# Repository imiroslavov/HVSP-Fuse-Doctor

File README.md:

# HVSP Fuse Doctor

The story began a long time ago. As of the moment that I am writing this README.md almost 21 years passed since then. 
I was really passionate to learn how to design and make my own hardware so I started learning how to make my own schematics, PCBs and how to program microcontrollers. 
Unfortunately I didn't knew how to properly program fuses and what was the difference between a crystal and clock oscillator so I ended up with a pile of "dead" microcontrollers. 
Back in these days I had a self made High-voltage programmer (The almighty "ByteBlaster+". I will post schematics and board design on another repository) but nowadays I have no place to plug it in since LPT ports are long time out of use in modern computing. 
I was developing a Low-ohm continuity tester with ATtiny2313 and accidentally bricked the MCU in my personal "old-school style" way (I've pulled my beard at least 1cm longer) and guess what... 
It was the last one in the box that was alive. So the journey began. 
I've ended up finding a lot of schematics and information, but most of it was related to using Arduino which for me was just a big "Ehh!". 
I found a few blog posts which helped me to design the device to be dependent on the power supply only (credits on the end of the page).

## Pinout

| PIN  | AVR | HVSP |
| ------------- | ------------- | ------------- |
| 1 | PC5 | **12V / RST** |
| 2 | PC0 | **SDI** |
| 3 | PC1 | **SII** |
| 4 | PC2 | **SDO** |
| 5 | PC3 | **SCI** |
| 6 | PC4 | **5V / VCC** |
| 7 | GND | **GND** |

## Schematics
This is the base schematic. Version 2 contains additional header connected to PD1 and GND which is used for RS232 communication and can be omitted. Thus the connector it's not shown here because it is optional.

## Board prototype v1 (dual power supply 5V/12V)
|                                                    Bottom layer                                                    |                                                              Top view                                                               |
|:------------------------------------------------------------------------------------------------------------------:|:-----------------------------------------------------------------------------------------------------------------------------------:|
|  |  |

Please note that the main.sch has additional sheet containing the mounting pads and connectors not shown in the schematics diagram above. They are there, but feel free to change them to make your own design (I've used one of those power supplies for external SATA disk drive readers that provide 5 and 12 volts simultaneously (DIN6)). 

## Notes
If the system still does not answer for a simple ISP programmer, that means the MCU has damaged hardware SPI, other damage or bad EEPROM.

Thanks to Peter Fleury at http://www.peterfleury.epizy.com/ for the original schematics and code. I've changed it of course but it is based on his work.

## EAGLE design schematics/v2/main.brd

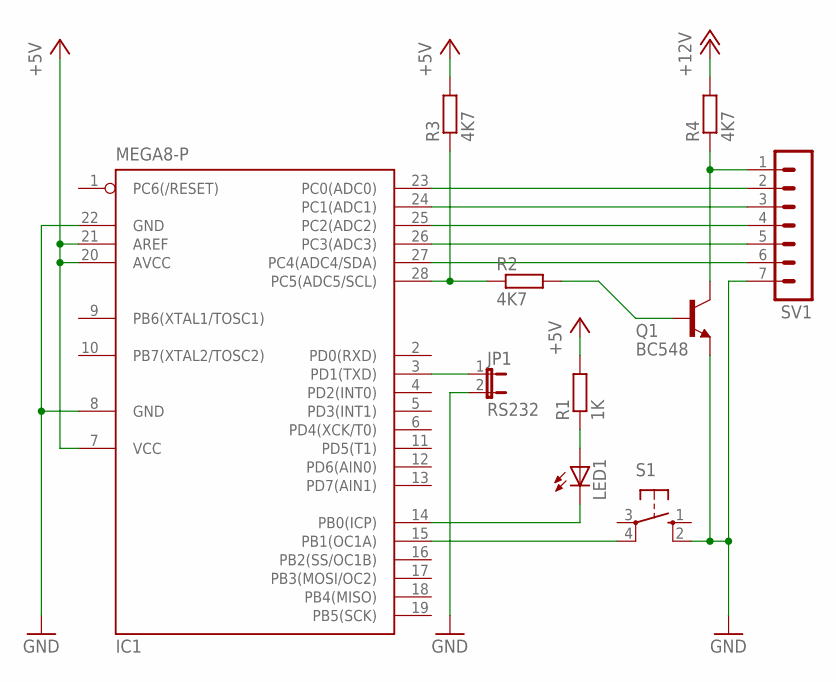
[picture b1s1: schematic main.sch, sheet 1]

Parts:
IC1: MEGA8-P; DIL28-3
JP1: RS232; JP1
LED1: LED5MM
Q1: BC548; TO92-EBC
R1: 1K; 0204/7
R2, R3, R4: 4K7; 0204/7
S1: 40-XX; B3F-40XX
SV1: MA07-1

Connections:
+5V: IC1.7 (VCC), IC1.20 (AVCC), IC1.21 (AREF), R1.2, R3.2; also elsewhere on the board
+12V: R4.2; also elsewhere on the board
GND: IC1.8 (GND), IC1.22 (GND), JP1.2, Q1.E, S1.2 (S1), SV1.7; also elsewhere on the board
unnamed: IC1.15 (PB1(OC1A)), S1.4 (P1)
unnamed: IC1.14 (PB0(ICP)), LED1.K (C)
unnamed: LED1.A, R1.1
unnamed: IC1.27 (PC4(ADC4/SDA)), SV1.6
unnamed: Q1.B, R2.2
unnamed: Q1.C, R4.1, SV1.1
unnamed: IC1.28 (PC5(ADC5/SCL)), R2.1, R3.1
unnamed: IC1.26 (PC3(ADC3)), SV1.5
unnamed: IC1.25 (PC2(ADC2)), SV1.4
unnamed: IC1.24 (PC1(ADC1)), SV1.3
unnamed: IC1.23 (PC0(ADC0)), SV1.2
unnamed: IC1.3 (PD1(TXD)), JP1.1

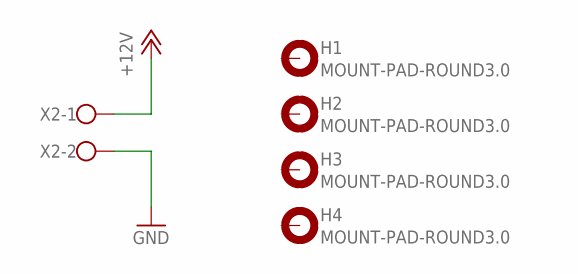
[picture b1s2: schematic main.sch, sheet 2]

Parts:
H1, H2, H3, H4: MOUNT-PAD-ROUND3.0; 3,0-PAD
X2: W237-102

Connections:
+12V: X2.1; also elsewhere on the board
GND: X2.2; also elsewhere on the board

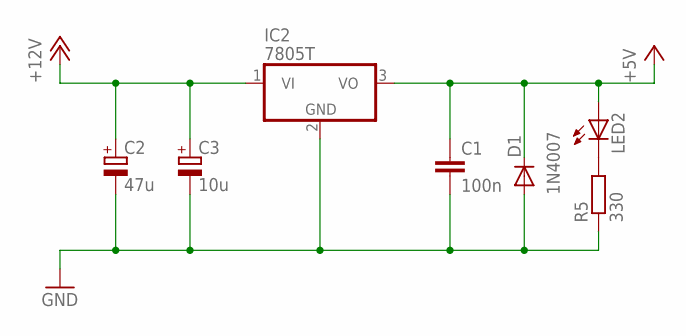
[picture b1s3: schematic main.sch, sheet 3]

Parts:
C1: 100n; C025-025X050
C2: 47u; E2,5-6
C3: 10u; E2,5-6
D1: 1N4007; D-7.5
IC2: 7805T; TO220H
LED2: LED5MM
R5: 330; 0204/7

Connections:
+5V: C1.1, D1.C, IC2.3 (VO), LED2.A; also elsewhere on the board
+12V: C2.+, C3.+, IC2.1 (VI); also elsewhere on the board
GND: C1.2, C2.-, C3.-, D1.A, IC2.2 (GND), R5.1; also elsewhere on the board
unnamed: LED2.K (C), R5.2

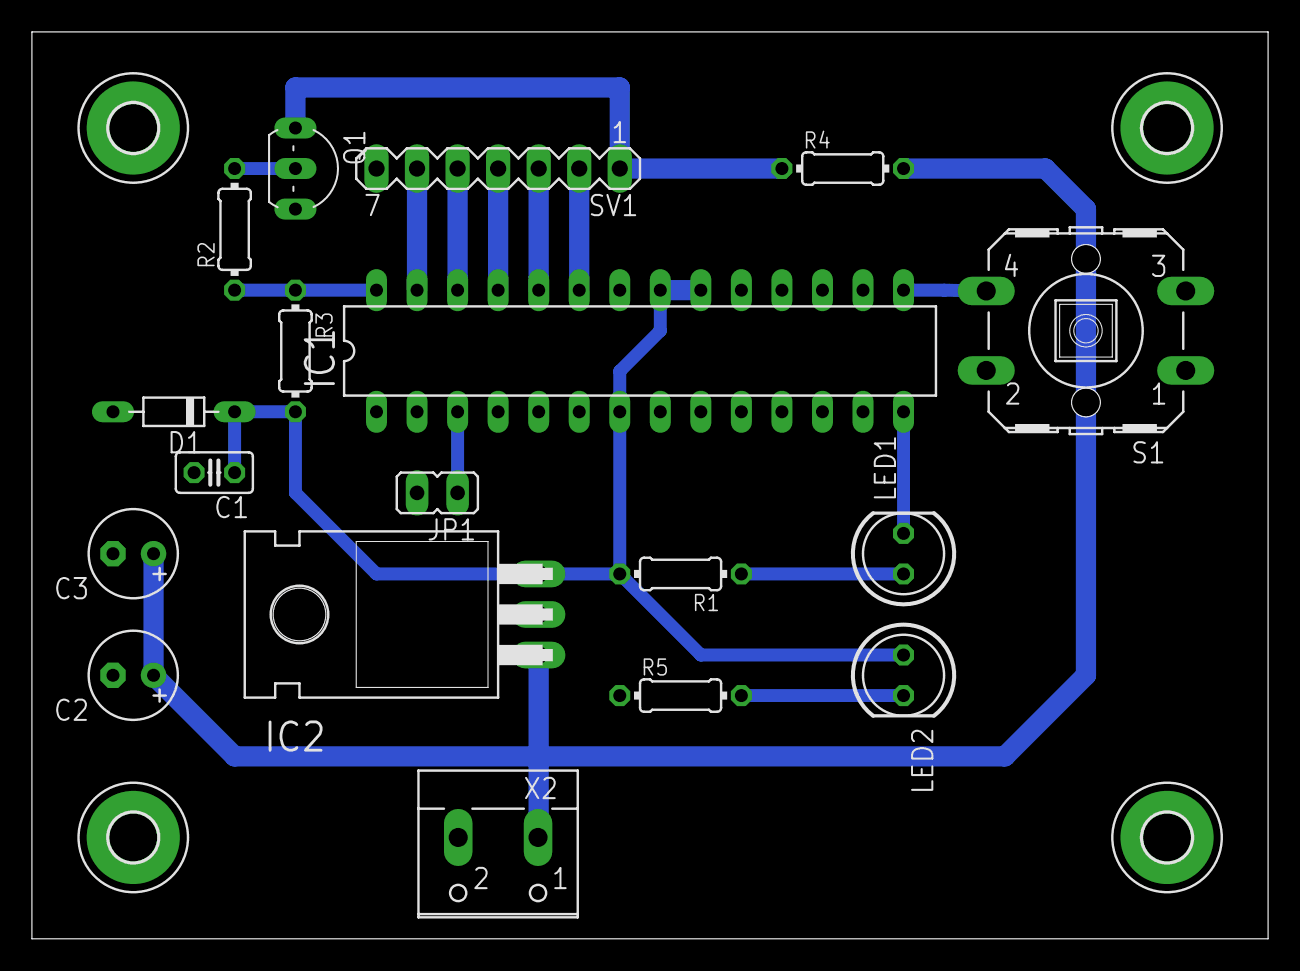
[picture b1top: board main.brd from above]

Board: 2 copper layers, 77.5 x 56.8 mm, 22 parts (0 on the bottom side), 16 nets.

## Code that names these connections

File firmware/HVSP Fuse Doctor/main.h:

#ifndef MAIN_H_
#define MAIN_H_

/*
* Port/Pin defines, adapt to your selected AVR and circuit
*/
#define HVSP_SDI_OUT PORTC
#define HVSP_SDI_DDR DDRC
#define HVSP_SDI     PC0 // Serial Data Input on target

#define HVSP_SII_OUT PORTC
#define HVSP_SII_DDR DDRC
#define HVSP_SII     PC1 // Serial Instruction Input on target

#define HVSP_SDO_OUT PORTC
#define HVSP_SDO_IN  PINC
#define HVSP_SDO_DDR DDRC
#define HVSP_SDO     PC2 // Serial Data Output on target

#define HVSP_SCI_OUT PORTC
#define HVSP_SCI_DDR DDRC
#define HVSP_SCI     PC3 // Serial Clock Input on target

#define HVSP_VCC_OUT PORTC
#define HVSP_VCC_DDR DDRC
#define HVSP_VCC     PC4 // VCC to target

#define HVSP_RST_OUT PORTC
#define HVSP_RST_DDR DDRC
#define HVSP_RST     PC5 // +12V to reset pin on target (inverted through NPN transistor)

#define LED_OUT      PORTB
#define LED_DDR      DDRB
#define LED_PIN      PB0 // LED to show result

#define SWITCH_OUT   PORTB
#define SWITCH_DDR   DDRB
#define SWITCH_IN    PINB
#define SWITCH_PIN   PB1 // Push button to start fuse restore

#define ZEROINPUTS() HVSP_SDI_OUT &= ~(1 << HVSP_SDI); \
                     HVSP_SII_OUT &= ~(1 << HVSP_SII)

/*
* Structure to hold signature and default fuse bits of target to be programmed
* See MCU data sheet or avr-libc include files iotnxx.h for the values of LFUSE_DEFAULT, HFUSE_DEFAULT, EFUSE_DEFAULT
* or use Atmel AVR Fuse Calculator: http://www.engbedded.com/fusecalc/
*/
typedef struct TARGET_MCU_INFO_struct {
    uint8_t signature[3];
    uint8_t fuseLowBits;
    uint8_t fuseHighBits;
    uint8_t fuseExtendedBits;
} TARGET_MCU_INFO_t;

#endif /* MAIN_H_ */

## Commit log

2025-02-14 Project initialization
2025-02-14 Firmware prototype (WIP)
2025-02-14 Additional gitignore rules
    Adding .gitignore config suitable for Microchip Studio. Thanks to Christopher McClellan (https://github.com/rubberduck203)
2025-02-17 Adding backstory
2025-02-17 Adding schematics v1
2025-02-17 Adding assets
2025-02-17 Updating assets
2025-02-17 Adding schematics, board and credits
2025-02-17 Of course there will be a typo
2025-02-17 Code cleanup
2025-02-17 Update README.md
    Prototype v2 will have a single power source and voltage regulators for 5V and 12 V
2025-02-17 Set global project configurations
2025-02-17 Adding pinout information
2025-02-18 Upload fritzing like PCB
2025-02-18 Adding fritzing style board to the readme
2025-02-18 Working on version 2
2025-02-18 Add "open hardware" logo
2025-02-19 Cosmetic changes
2025-02-20 Changes in wording
2025-02-22 Version 2 with power supply 12V only
2025-02-26 Adding notes to README.md
2025-02-26 Version 2 with single power supply (12V) - WIP
2025-02-26 Updating v1 assets
2025-02-26 Adding pinout to the fritzing asset
2025-02-26 Adding info about schematics of v2
2025-02-26 Some cosmetic changes
2025-02-26 Updating schematics for v2
2025-02-26 Rewording
